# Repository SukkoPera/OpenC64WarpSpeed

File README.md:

# OpenC64WarpSpeed
OpenC64WarpSpeed is an Open Hardware Fast Loader cartridge for the Commodore 64 and 128 home computers.

> [!CAUTION]
> **THIS CART CURRENTLY HAS A DESIGN FLAW THAT MIGHT CAUSE DAMAGE TO IT OR TO YOUR C64 - PLEASE DO NOT USE!**
>
> See [#3](https://github.com/SukkoPera/OpenC64WarpSpeed/issues/3) for more information.

## Summary
OpenC64WarpSpeed is a clone of the *WarpSpeed* cartridge, a Fast Loader cartridge released by the *Alien Technology Group* and distributed by *Cinemaware* in early 1988. Its main function is to provide turbo speed to all disk functions, in a similar way to the better-known *Epyx Fastload* cartridge. Since it was a bit late to the party, it didn't gain as much fame.

I learned about the existance of this cartridge when my friend Terje suggest me to watch [this video by Adrian](https://www.youtube.com/watch?v=6bqKQADHF_Y): it outperformed JiffyDOS, so I started to look around for information. This way I found out that it's one of only two cartridges of its kind to have native support for the Commodore 128 (the other being the Mach 128) and I even found the original schematics (including the PCB layout!) in the manual. So I just decided to remake it.

First I sticked to the original schematics and routing, then I did a second version with a few improvements.

## Features
* Fast serial I/O (1541, 1571 and with WarpSpeed v2 also for 1581 floppy disk drives)
* DOS wedge
* Monitor (Pi-sign)
* File and disk copier
* Disk sector editor
* Utility commands using arrow up - allowing to kill fastload and OLD
* Native Commodore 128 mode
* Reset button

Check out [this page on World of Jani](http://blog.worldofjani.com/?p=5043) and  [this nice page and video by Obliterator918](https://www.obliterator918.com/the-warp-speed-cartridge-from-cinemaware-is-nice/) for more information about the features of this cartridge.

## Assembly
There are two versions of this cartridge:
- The version on the *original* branch is an almost 1:1 copy of the original PCB. The only changes are to fit a switch and a pushbutton that are common these days. If you use this card, you will need to flash the *raw* ROMs. You are supposed to use a 27128 EPROM with this, but you can use a 27C512 EEPROM by putting the ROM in the upmost 16K. To make it easier: just concatenate the ROM to itself 4 times (until it's 64K) and flash that file.
- The version on the *master* branch has some improvements. First of all, the address and data lines have been unscrambled, so you will need to flash the *unscrambled* ROMs. Actually you can use two ROMs at the same time, you can switch between them with *SW3*. You can either use a 27256 or 27512 EPROM (use the upper 32K on the latter). Other small improvements include decoupling caps on the EPROM and flip-flop ICs and using a ground plane.

ROM files are available [in the ROMs folder](https://github.com/SukkoPera/OpenC64WarpSpeed/tree/master/ROMs).

I admit it is not clear at all to me how this cartridge does its job but, as far as I know, all cartridges of this kind play nasty tricks with the control lines, therefore I recommend sticking to the original values for all components, as they might influence the timing of signals.

## Releases
If you want to get this board produced, you are recommended to get [the latest release](https://github.com/SukkoPera/OpenC64WarpSpeed/releases) rather than the current git version, as the latter might be under development and is not guaranteed to be working.

Every release is accompanied by its Bill Of Materials (BOM) file and any relevant notes about it, which you are recommended to read carefully.

Releases of the *original* branch get tagged *vXorig*, while improved versions get tagged just *vX*.

**I am not providing ready-to-use gerber files**. If all you want is **to get boards made, I would really appreciate if you did so [in a way that supports the project](#support-the-project)**.

## Enclosure
A 3D-printable enclosure is currently available for this board, it was kindly contributed by Alexander Schupp and it is available in the [enclosure](./enclosure) folder.

## License
*(I am not sure I can claim any copyright on this, as the actual schematics this is based on belong to the *Alien Technology Group* - or whoever has that right now, definitely not me. So the claim below is going to be more of a declaration of intent, in the sense that I would like that everything that is derived from my work stays open and free.)*

The OpenC64WarpSpeed documentation, including the design itself, is copyright &copy; SukkoPera 2020.

OpenC64WarpSpeed is Open Hardware licensed under the [CERN OHL v. 1.2](http://ohwr.org/cernohl).

You may redistribute and modify this documentation under the terms of the CERN OHL v.1.2. This documentation is distributed *as is* and WITHOUT ANY EXPRESS OR IMPLIED WARRANTIES whatsoever with respect to its functionality, operability or use, including, without limitation, any implied warranties OF MERCHANTABILITY, SATISFACTORY QUALITY, FITNESS FOR A PARTICULAR PURPOSE or infringement. We expressly disclaim any liability whatsoever for any direct, indirect, consequential, incidental or special damages, including, without limitation, lost revenues, lost profits, losses resulting from business interruption or loss of data, regardless of the form of action or legal theory under which the liability may be asserted, even if advised of the possibility or likelihood of such damages.

A copy of the full license is included in file [LICENSE.pdf](LICENSE.pdf), please refer to it for applicable conditions. In order to properly deal with its terms, please see file [LICENSE_HOWTO.pdf](LICENSE_HOWTO.pdf).

The contact points for information about manufactured Products (see section 4.2) are listed in file [PRODUCT.md](PRODUCT.md).

Any modifications made by Licensees (see section 3.4.b) shall be recorded in file [CHANGES.md](CHANGES.md).

The Documentation Location of the original project is https://github.com/SukkoPera/OpenC64WarpSpeed/.

## Selling the board
**The license allows you to sell these boards**. I have nothing against that **as long as you do so at an "ethical" price**. I understand you want to make some money, but please note that you are getting this all for free, you had no development costs and you invested no time in this project. You are making money with someone else's work, who has the desire to allow everybody to get a board at a REASONABLE price, so please keep your margin low. I estimate that **having a few of these boards produced and assembled costs about 3€ per board**, so let me add the following request: **if this board is sold at more than 8€ (or equivalent in your currency), I strongly encourage you to donate 25% of your earning to a LEGITIMATE charity** of some kind, like curing cancer for example. This amount has been set in May 2020 and will be updated, should the value of the Euro vary significantly.

Also, please **do not remove the credits, URL and license statement**. There is **no reason do so**, you have the right to sell this board, there is no need to pretend you got it somewhere else. Ironically, If you removed those, you'd lose that right as you'd be violating the license terms.

## Support the Project
If you want to support the project, you can order the boards from PCBWay through these links:

You get my gratitude and cheap, good quality PCBs, professionally-made. I get some credit that will help with this and [other projects](https://www.pcbway.com/project/member/shareproject/?bmbid=41100). You won't even have to worry about the various PCB options, it's all pre-configured for you!

Also, if you still have to register to that site, [you can use this link](https://www.pcbway.com/setinvite.aspx?inviteid=41100) to get some bonus initial credit (and yield me some more).

You can also buy me a coffee if you want:

## Get Help
If you need help or have any questions or suggestions, you can join `#OpenRetroWorks` on FreeNode through your favorite IRC client or [the webchat](https://webchat.freenode.net/), or [the official Telegram group](https://t.me/joinchat/HUHdWBC9J9JnYIrvTYfZmg).

## Dedication
This project is dedicated to my friend Terje, who let me know about this cartridge and tested the boards. I hope this makes it easier for you to fight your battle :).

## Thanks
- replay resources for [hosting the documentation](https://rr.pokefinder.org/wiki/WarpSpeed) that allowed the recreation of this cartridge.
- iAN CooG for decoding the ROMs.
- MayhemUK64 for providing [a review of the original cartridge](http://www.mayhem64.co.uk/cartpower.htm), which was integrated in the text above.

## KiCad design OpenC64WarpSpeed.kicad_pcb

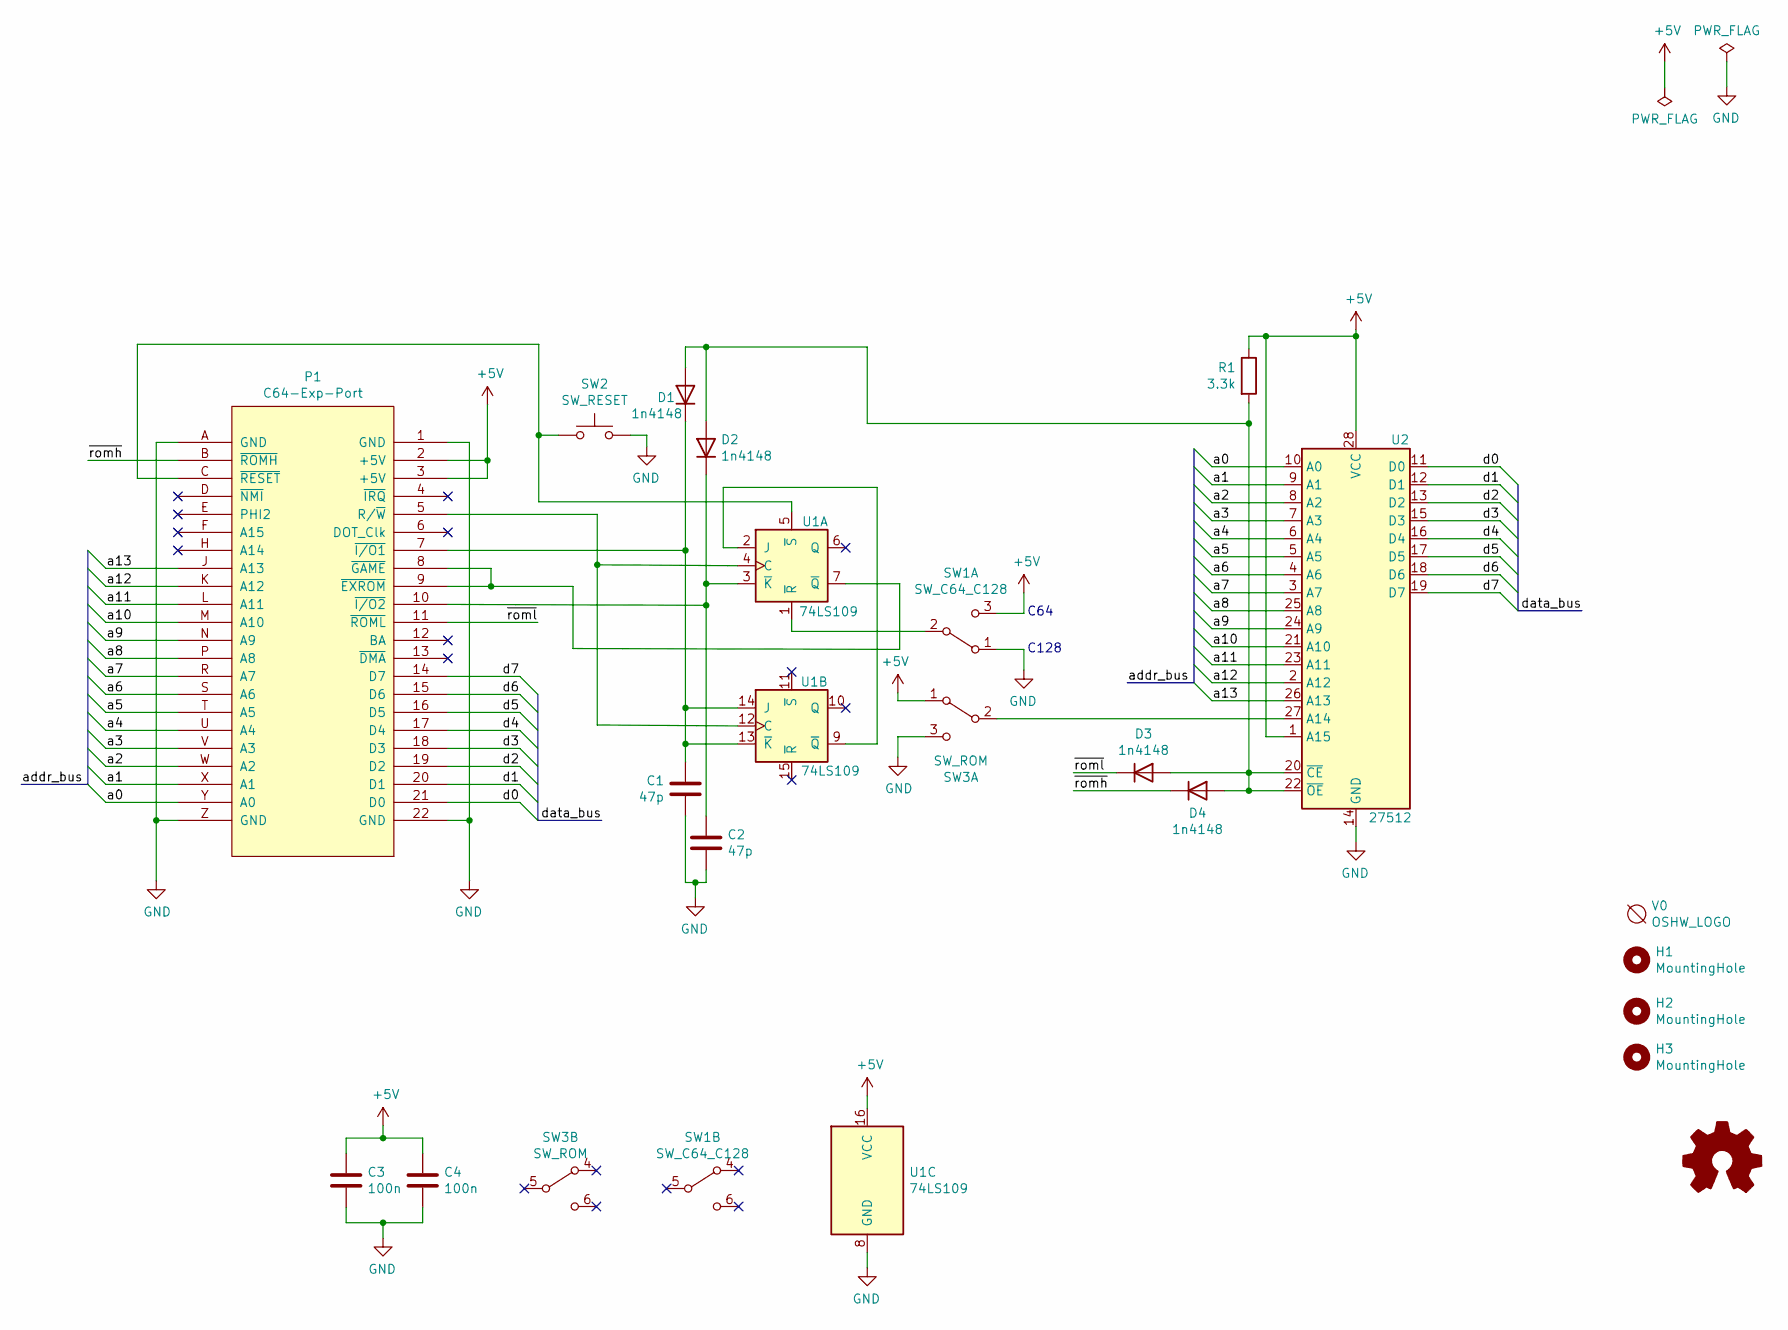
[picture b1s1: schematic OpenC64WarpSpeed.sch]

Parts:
C1, C2: 47p; C_Disc_D7.5mm_W2.5mm_P5.00mm
C3, C4: 100n; C_Disc_D7.5mm_W2.5mm_P5.00mm
D1, D2, D3, D4: 1n4148; D_DO-35_SOD27_P7.62mm_Horizontal
H1: MountingHole; MountingHole_6.4mm_M6
H2, H3: MountingHole; MountingHole_3.2mm_M3
P1: C64-Exp-Port; C64-Cart
R1: 3.3k; R_Axial_DIN0204_L3.6mm_D1.6mm_P7.62mm_Horizontal
SW1: SW_C64_C128; SW_DPDT
SW2: SW_RESET; SW_PUSH_6mm
SW3: SW_ROM; SW_DPDT
U1: 74LS109; DIP-16_W7.62mm_Socket_LongPads
U2: 27512; DIP-28_W15.24mm_Socket_LongPads
V0: OSHW_LOGO; OSHW-Logo_7.5x8mm_Copper

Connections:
+5V: C3.1, C4.1, P1.2 (+5V), P1.3 (+5V), R1.1, SW1.3 (C), SW3.1 (A), U1.16 (VCC), U2.1 (A15), U2.28 (VCC)
/a0: P1.Y (A0), U2.10 (A0)
/a1: P1.X (A1), U2.9 (A1)
/a2: P1.W (A2), U2.8 (A2)
/a3: P1.V (A3), U2.7 (A3)
/a4: P1.U (A4), U2.6 (A4)
/a5: P1.T (A5), U2.5 (A5)
/a6: P1.S (A6), U2.4 (A6)
/a7: P1.R (A7), U2.3 (A7)
/a8: P1.P (A8), U2.25 (A8)
/a9: P1.N (A9), U2.24 (A9)
/a10: P1.M (A10), U2.21 (A10)
/a11: P1.L (A11), U2.23 (A11)
/a12: P1.K (A12), U2.2 (A12)
/a13: P1.J (A13), U2.26 (A13)
/d0: P1.21 (D0), U2.11 (D0)
/d1: P1.20 (D1), U2.12 (D1)
/d2: P1.19 (D2), U2.13 (D2)
/d3: P1.18 (D3), U2.15 (D3)
/d4: P1.17 (D4), U2.16 (D4)
/d5: P1.16 (D5), U2.17 (D5)
/d6: P1.15 (D6), U2.18 (D6)
/d7: P1.14 (D7), U2.19 (D7)
/~romh: D4.1 (K), P1.B (~ROMH)
/~roml: D3.1 (K), P1.11 (~ROML)
GND: C1.2, C2.2, C3.2, C4.2, P1.1 (GND), P1.22 (GND), P1.A (GND), P1.Z (GND), SW1.1 (A), SW2.2, SW3.3 (C), U1.8 (GND), U2.14 (GND)
unnamed: C1.1, D1.1 (K), P1.7 (~I/O1), U1.13 (~K), U1.14 (J)
unnamed: C2.1, D2.1 (K), P1.10 (~I/O2), U1.3 (~K)
unnamed: D1.2 (A), D2.2 (A), D3.2 (A), D4.2 (A), R1.2, U2.20 (~CE), U2.22 (~OE)
unnamed: P1.5 (R/~W), U1.4 (C), U1.12 (C)
unnamed: P1.8 (~GAME), P1.9 (~EXROM), U1.7 (~Q)
unnamed: P1.C (~RESET), SW2.1, U1.5 (~S)
unnamed: SW1.2 (B), U1.1 (~R)
unnamed: SW3.2 (B), U2.27 (A14)
unnamed: U1.2 (J), U1.9 (~Q)

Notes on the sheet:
C128
C64

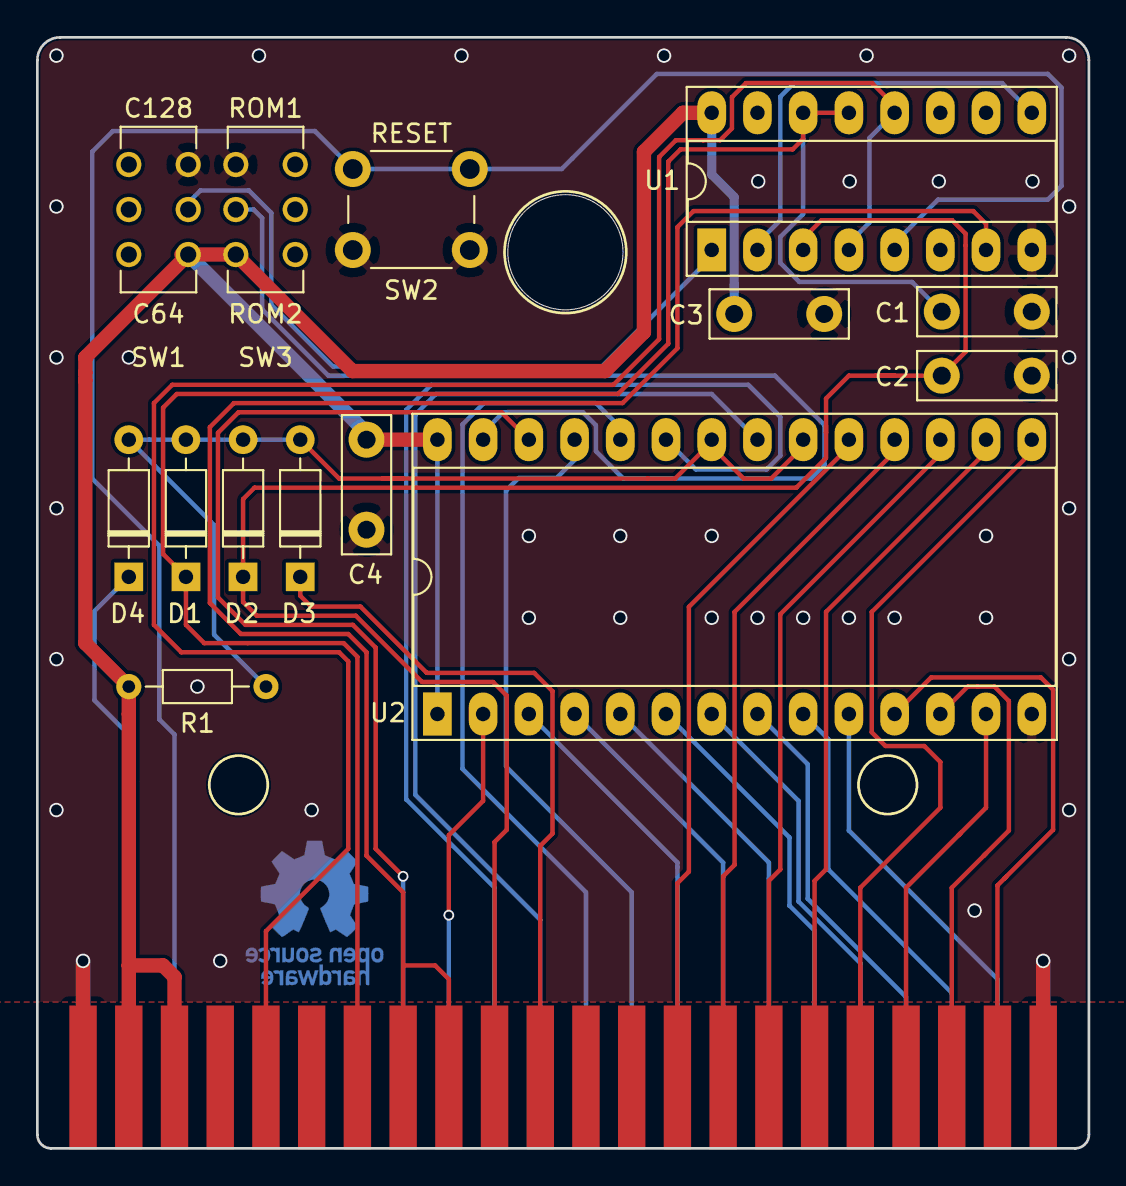
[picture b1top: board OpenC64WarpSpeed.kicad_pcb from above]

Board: 2 copper layers, 58.4 x 61.7 mm, 19 parts (1 on the bottom side), 35 nets.

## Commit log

2020-03-27 Initial commit Original PCB is recreated pretty closely. But we can improve that! :)
2020-03-27 Improving the design... - Use ground plane - Add decoupling caps - Avoid scrambling the address and data buses - Switch to 27512
2020-03-27 Almost there
2020-03-27 I guess we're good, just need to work on the ground plane yet
2020-03-28 Switch to a 27256 EPROM, but a 27512 can still be used (use upper 32K)
2020-03-28 Yeah
2020-03-28 We'll call it good!
2020-03-28 Let's get prototypes made
2020-03-28 Minor fixes and add license claim
2020-03-28 Change version number
2020-03-28 Add license claim
2020-03-29 Add license and README
2020-03-29 Add OSHW logo
2020-03-29 Reorganize ROMs and docs
2020-03-29 Update ROMs path and info
2020-03-29 Fix ROMs path
2020-03-29 Typo
2020-05-30 Reorder ROMs
2020-05-30 Add renders
2020-05-30 Add second board link
2020-05-31 Add note on selling the board
2020-05-31 Restriction -> Request :)
2020-07-14 Remove decoder executable to avoid false positives by antiviruses Sigh, I'll make this available in the Releases section
2020-10-25 Fix capacitor value: 470nF -> 47pF - Thanks @svenpetersen1965
2024-06-01 Add enclosure, videos and info
2024-06-01 Add design flaw warning
2025-06-19 Mention Mach 128

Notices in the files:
OpenC64WarpSpeed.kicad_pcb:
Licensed under CERN OHL v.1.2
